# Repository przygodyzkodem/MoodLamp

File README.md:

# MoodLamp

MoodLamp is an ESP8266 based WS2812B addressable LED controller. It's key features are:
- 55 different togglable light effects
- adjustable light color
- adjustable brightness
- quick on/off toggle
- easy configuration via captive portal
- minimalistic hardware design - cheap and easy to assemble and to install in your home

## Demo / Use Case Examples

Demo video (click to watch, don't forget to slap like :P ):

Litophane lamp (gift for my lovely girlfriend):

3D Printer project kudos to GrkMangas from Thingiverse: [https://www.thingiverse.com/thing:2730082](https://www.thingiverse.com/thing:2730082)

## How to assemble your own Mood Lamp

In this repository you can find several types of resources. I plan to create few form factors of hardware and several software versions. The common thing for all of them will be the usage of ESP8266 module and Arduino code to drive addressable LEDs (e.g. WS2812B). To create your own Mood Lamp, please follow the steps listed below. Please note that each hyperlink will take you to another part of this repository which will contain another piece of documenation that will provide you with further details.

1. Pick your hardware version:
- you can build circuit out of Arduino modules based on Fritzing layout which you can find here
- you can assemble a NodeMCU shield with resources in folder: 
2. Select your software:
- currently only implementation using Blynk platform available: [LINK](https://github.com/przygodyzkodem/MoodLamp/tree/master/Software/Blynk)
3. Select proper power supply:
- all of the hardware designs will require power supply with 5V DC voltage
- to calculate the current required by your circuit, you can use the following equation: (60mA x N) + 120mA, where N is number of WS2812B diodes in your project
- please note, that if your project current requirement goes above few Amperes it is crossing a border where it becomes dangerous, consider splitting the project into few, separately powered modules
4. Install required software to control the Mood Lamp:
- currently it means installing Blynk app and properly configuring your project, check instructions in Software section for detailed instructions
5. Design your enclosure or use some ideas from repository.

## Plans / ToDo:

- add documentation for Fritzing layout / basic connections on breadboard
- add documentation for Blynk software implementation
- add documentation for Hardware version (NodeMCU shield)
- design a 3D printed enclosure for NodeMCU + hardware shield

## Contributing

If you find any errors/bugs/problems with either hardware or software, please create a new issue in this repository to let me know. If you have an idea for a new feature or hardware or software variant, please also use Issues section so we can discuss it.

## License
MoodLamp project is available under the MIT License. See the [LICENSE](https://github.com/przygodyzkodem/MoodLamp/blob/master/LICENSE) file for more info.

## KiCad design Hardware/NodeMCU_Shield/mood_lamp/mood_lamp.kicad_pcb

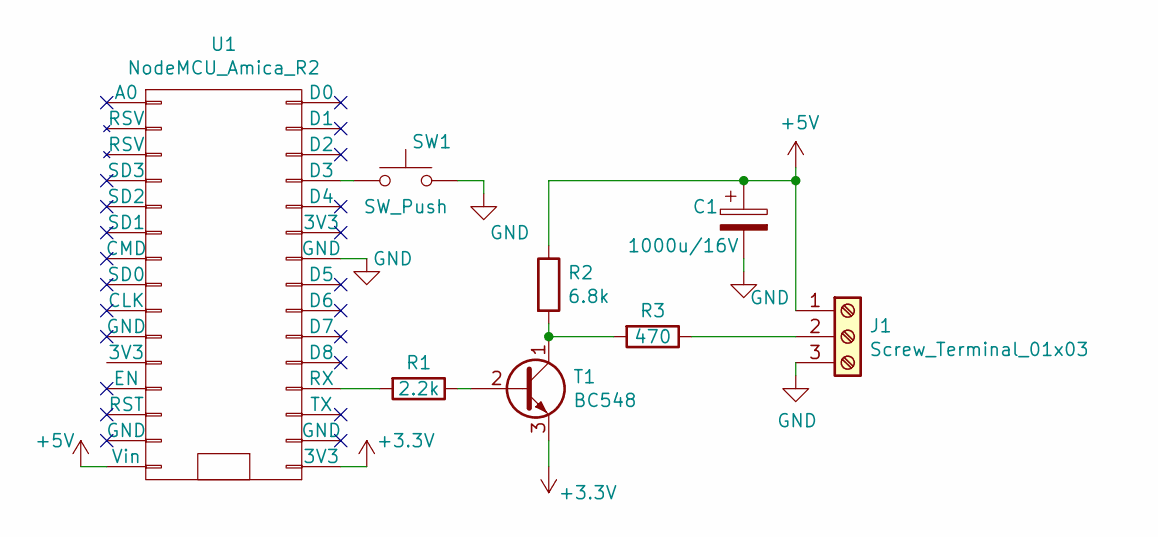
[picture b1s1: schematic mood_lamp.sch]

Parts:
C1: 1000u/16V; CP_Radial_D10.0mm_P7.50mm
J1: Screw_Terminal_01x03; TerminalBlock_bornier-3_P5.08mm
R1: 2.2k; R_Axial_DIN0207_L6.3mm_D2.5mm_P7.62mm_Horizontal
R2: 6.8k; R_Axial_DIN0207_L6.3mm_D2.5mm_P7.62mm_Horizontal
R3: 470; R_Axial_DIN0207_L6.3mm_D2.5mm_P7.62mm_Horizontal
SW1: SW_Push; SW_PUSH_6mm_H5mm
T1: BC548; TO-92_Inline
U1: NodeMCU_Amica_R2

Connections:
+3V3: T1.3 (E), U1.16 (3V3)
+5V: C1.1, J1.1, R2.1, U1.15 (Vin)
GND: C1.2, J1.3, SW1.2, U1.24 (GND)
unnamed: J1.2, R3.1
unnamed: R1.1, T1.2 (B)
unnamed: R1.2, U1.19 (RX)
unnamed: R2.2, R3.2, T1.1 (C)
unnamed: SW1.1, U1.27 (D3)

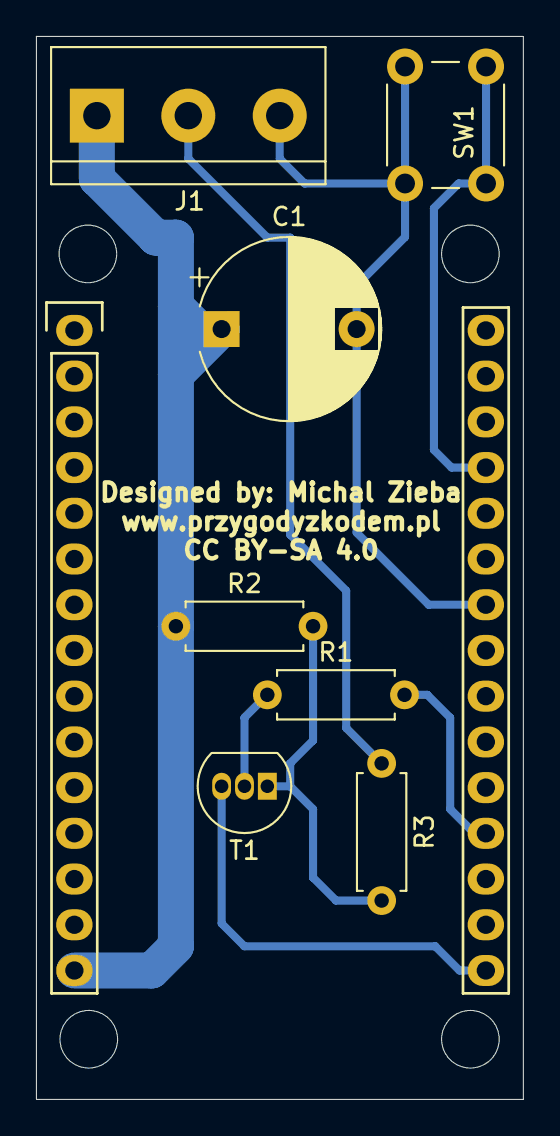
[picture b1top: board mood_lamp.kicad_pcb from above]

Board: 2 copper layers, 27.1 x 59.1 mm, 8 parts (0 on the bottom side), 8 nets.

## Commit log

2020-01-02 Initial version of project based on Blynk
2020-01-02 Fixed bug with not turning on light before connecting to WiFi. Started to divide code from setup into smaller functions.
2020-01-25 Fixed problem with rewriting Blynk token to EEPROM (incorrect value was saved to EEPROM on 2nd and each next usage of WiFiManager captive portal).
2020-01-25 Disabled blue LED built into ESP8266 module.
2020-01-25 Moved Blynk token length to constant value definition. Added sending correct MoodLamp state to Blynk so app reflects it on lamp restart.
2020-01-25 Create LICENSE
2020-01-26 Added basic reset button action - resetting WiFiManager to allow easier reconnecting to another WiFiNetwork or entering another Blynk Token. TODO: Change reset button to be triggered by long press ac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
2020-01-26 Changed reset button pin assignment to make PCB prototyping easier. Added KiCAD project with NodeMCU shield schematic and PCB design
2020-01-26 Added Fritzing layout for design utilizing Logic Level Shifter module.
2020-02-21 Updated fritzing layouts. Fixed some issues with PCB design. Generated Gerber files.
2020-02-29 Added image resources for readme file
2020-02-29 Reduced image size
2020-02-29 Moved software implementations to separate folder
2020-03-17 Moved files, added Fritzing layout image file
2020-03-17 Added QR Code that allows to clone Blynk project configuration into Blynk mobile app
2020-03-17 Added external libraries to allow easier installation of dependencies by copy-pasting
2020-03-17 Add instructions for assembling Blynk based software variant.

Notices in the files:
Hardware/NodeMCU_Shield/mood_lamp/mood_lamp.kicad_pcb:
CC BY-SA 4.0
